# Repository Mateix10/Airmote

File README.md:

# Airmote

Control any IR device and monitor room temperature, pressure and humidity with Home Assistant.

# Zine

# Why?

I always wanted to add my older devices that aren't compatible with Home Assistant to my automations. I want to turn my old stereo on when I start playing music, without having to reach for the half-broken remote.

# Firmware

For the firmware, use [ESPHome](https://esphome.io)

[Install guide](https://esphome.io/guides/getting_started_hassio/)

Code for the BME280 temperature sensor:

```yaml
sensor:
  - platform: bme280_i2c
    temperature:
      name: "BME280 Temperature"
    pressure:
      name: "BME280 Pressure"
    humidity:
      name: "BME280 Humidity"
```
... and for the IR:

```yaml
remote_transmitter:
  pin: GPIOXX
  carrier_duty_percent: 50%

climate:
  - platform: REPLACEME     # you need to replpace the platform to your AC. See esphome documentation for more
    name: "Living Room AC"
    sensor: room_temperature
    use_fahrenheit: false
```

Note: this is untested code.

# Schematic and PCB

The schematic and PCB are pretty simple, just connecting the LEDs to a 2n2222 transistor and accompanying resistors for protection.

The BME 280 sensor is connected trough I2C. It's connected that way becaouse it simplifies the PCB and the sensor doesn't need fast data.

# Case

I went for a industrial design as this device is intended to be hidden away on a high surface, away from sight. The bottom and top of the case are held by m2 screws along side bolts and heat inserts.

Designed in Fusion 360.
Files are available in 3D/Airmote.f3z

# BOM

|Item|Count|Price|Link|
|--|--|--|--|
|Seeed Studio XIAO ESP32-C6|1|$5.20|[Seeed Studio](https://www.seeedstudio.com/Seeed-Studio-XIAO-ESP32C6-p-5884.html)|
|**3mm 940nm IR LED***|4|$1.47/lot|[Aliexpress](https://www.aliexpress.com/item/1005002345587711.html)|
|**2N2222 transistor***|1|$3.75/lot|[Aliexpress](https://www.aliexpress.com/item/1005010396511377.html)  (Select 2n2222 in the listing)|
|**220 Ohm resistor***|1|$0.63/lot|[Aliexpress](https://www.aliexpress.com/item/1005002489867848.html) (Select 220R in the listing)|
|**47 Ohm resistor***|4|$0.63/lot|[Aliexpress](https://www.aliexpress.com/item/1005002489867848.html) (Select 47R in the listing)|
|BME280 sensor breakout board|1|$4.00|[Aliexpress](https://www.aliexpress.com/item/1005012601108975.html) (Select 5V or else it won't fit)|
|**Heat brass inserts***|4|$7.09/lot|[Aliexpress](https://www.aliexpress.com/item/1005006798286851.html) (Select M2(OD3mm) and 2mm length)|
|**M2 Screws***|4|$3.85/lot|[Aliexpress](https://www.aliexpress.com/item/4000038065691.html) (Select M2 10mm in the listing)|
|PCB|1|$2|[JLCPCB](https://jlcpcb.com)
|Shipping|-|$69.39|-|
|**Total**|-|$92.81|-| 

***ONLY** buy the listing of **bolded** items ONCE. Those are sold as a lot and you will be getting 50/100pcs per listing bought.

# Credits

[Hackclub Fallout](https://fallout.hackclub.com) - Founding

[Kicad](https://kicad.org) - Schematic and PCB design

[ESPHome](https://esphome.io) - Firmware

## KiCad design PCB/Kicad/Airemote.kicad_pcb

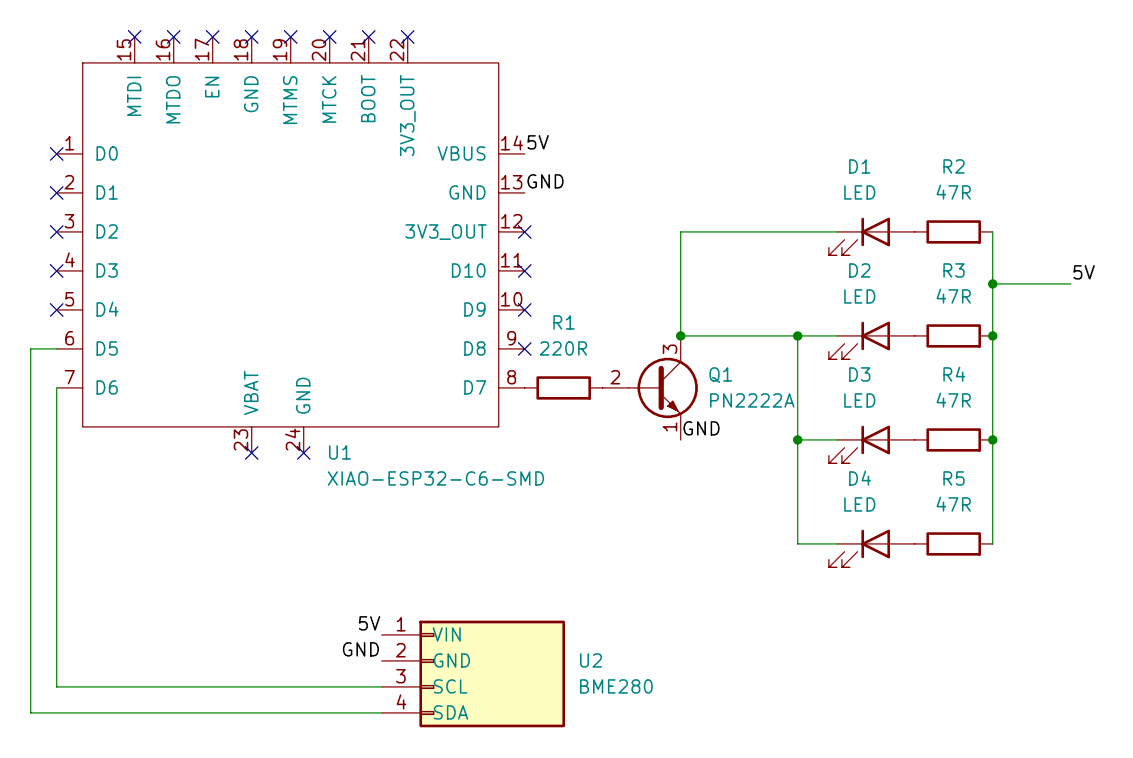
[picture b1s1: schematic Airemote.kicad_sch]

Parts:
D1, D2, D3: LED; LED_D3.0mm_Horizontal_O1.27mm_Z2.0mm_Clear
D4: LED; LED_D3.0mm_Clear
Q1: PN2222A; TO-92_Inline
R1: 220R; R_Axial_DIN0207_L6.3mm_D2.5mm_P10.16mm_Horizontal
R2, R3, R4, R5: 47R; R_Axial_DIN0207_L6.3mm_D2.5mm_P10.16mm_Horizontal
U1: XIAO-ESP32-C6-SMD; XIAO-ESP32-C6-DIP
U2: BME280; BME280_BreakOut

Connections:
/5V: R2.2, R3.2, R4.2, R5.2, U1.14 (VBUS), U2.1 (VIN)
/GND: Q1.1 (E), U1.13 (GND), U2.2 (GND)
unnamed: D1.2 (A), R2.1
unnamed: D1.1 (K), D2.1 (K), D3.1 (K), D4.1 (K), Q1.3 (C)
unnamed: D2.2 (A), R3.1
unnamed: D3.2 (A), R4.1
unnamed: D4.2 (A), R5.1
unnamed: Q1.2 (B), R1.2
unnamed: U1.6 (D5), U2.4 (SDA)
unnamed: U1.7 (D6), U2.3 (SCL)
unnamed: R1.1, U1.8 (D7)

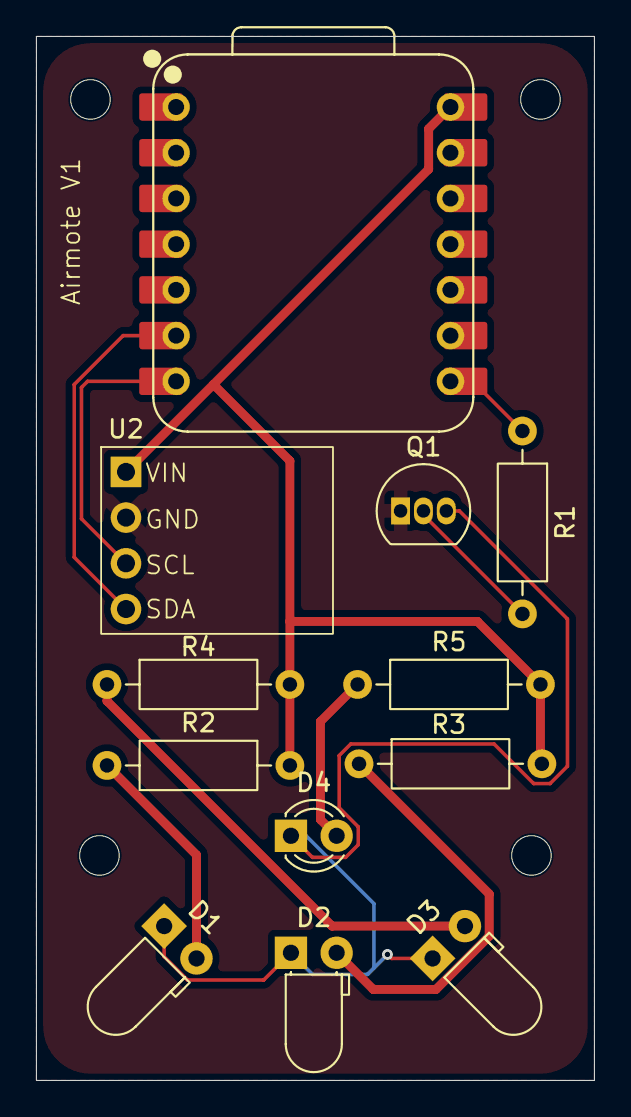
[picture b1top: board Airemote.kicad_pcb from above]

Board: 2 copper layers, 31.0 x 58.0 mm, 12 parts (0 on the bottom side), 11 nets.
